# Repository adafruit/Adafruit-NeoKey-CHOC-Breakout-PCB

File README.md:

## Adafruit NeoKey CHOC Breakout PCB

<a href="http://www.adafruit.com/products/5756"><br/>
Click here to purchase one from the Adafruit shop</a>

PCB files for the Adafruit NeoKey CHOC Breakout. 

Format is EagleCAD schematic and board layout
* https://www.adafruit.com/product/5756

### Description

The only thing better than a nice mechanical key, is one that also can glow any color of the rainbow - and that's what the Adafruit NeoKey Breakout will let you do! This little 0.75" x 0.95" PCB can fit one Kailh CHOC or compatible switch and make it easy to use with a breadboard or perfboard.

The breakout has a Kailh CHOC socket, which means you can plug in any CHOC-compatible switch instead of soldering it in. You may need a little glue to keep the switch in place; hot glue or a dot of epoxy worked fine for us. We also place a 1N4148 signal diode in series with the switch, so you can create key-grid matrices without worrying about ghosted keys.

Each breakout also has a single reverse-mount NeoPixel pointing up through the spot where many switches would have an LED to shine through. The input and output of the pixel are broken out so you can 'chain' these boards together and control them as one NeoPixel strand.

There's plenty of flexibility for any kind of use; each board has the following pin out:

* VDD (+) The power pin for the NeoPixel; provide 3 to 5VDC
* GND (-) The ground power pin for the NeoPixel, connect to ground
* In (I) and Out (O) The input and output to/from the NeoPixel, for chaining
* Switch Anode (A) - The 'positive' side of the switch+diode. If you're using the switch with a pull-up resistor, connect this pin to your microcontroller. If you're using a pull-down, connect this pin to your logic level power pin.
* Switch Cathode (C) - The 'negative' side of the switch+diode. If you're using the switch with a pull-up resistor, connect this pin to ground. If you're using a pull-down, connect this pin to your microcontroller.

There're two rows of 5-pin contacts on a 0.1" grid on both sides. Solder in both sides for mechanical stability; the two sides share the same pins except for one side is NeoPixel in and the opposite side has the out pin. For side-by-side wiring, we also have the cathode pin broken out on the sides, and another set of NeoPixel In/Out pins.

Please note, each order comes with one assembled PCB and a small stick of break-off header. Soldering is required to attach the header for breadboard use. A mechanical switch and key cap are not included! Use any CHOC-compatible switch. Note that Cherry/MX switches are not at all compatible with CHOC sockets.

### License

Adafruit invests time and resources providing this open source design, please support Adafruit and open-source hardware by purchasing products from [Adafruit](https://www.adafruit.com)!

Designed by Limor Fried/Ladyada for Adafruit Industries.

Creative Commons Attribution/Share-Alike, all text above must be included in any redistribution. 
See license.txt for additional details.

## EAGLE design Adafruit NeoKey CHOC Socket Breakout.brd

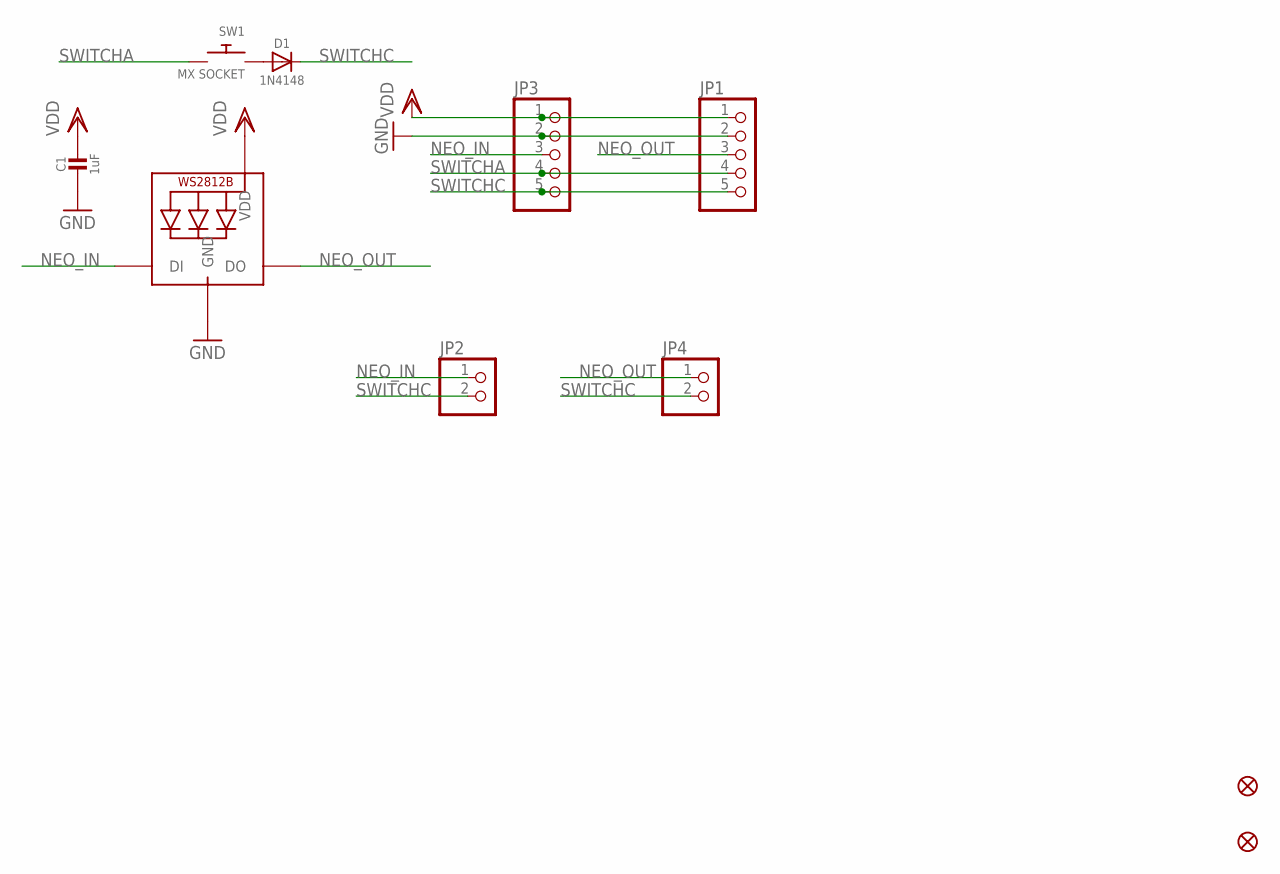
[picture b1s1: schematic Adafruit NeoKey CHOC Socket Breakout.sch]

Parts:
C1: 1uF; 0603-NO
D1: 1N4148; SOD-323
FID3, FID4: FIDUCIAL_1MM
JP1, JP3: HEADER-1X570MIL; 1X05_ROUND_70
JP2, JP4: HEADER-1X2ROUND; 1X02_ROUND
LED1: WS2812B_SK6812E; NEO3535_REVERSE
SW1: MX SOCKET; KAILH_CHOC_SOCKET

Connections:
GND: C1.2, JP1.2, JP3.2, LED1.3-GND (GND)
unnamed: D1.A, SW1.1
NEO_IN: JP2.1, JP3.3, LED1.4-DIN (DI)
NEO_OUT: JP1.3, JP4.1, LED1.2-DOUT (DO)
SWITCHA: JP1.4, JP3.4, SW1.2
SWITCHC: D1.C, JP1.5, JP2.2, JP3.5, JP4.2
VDD: C1.1, JP1.1, JP3.1, LED1.1-VDD (VDD)

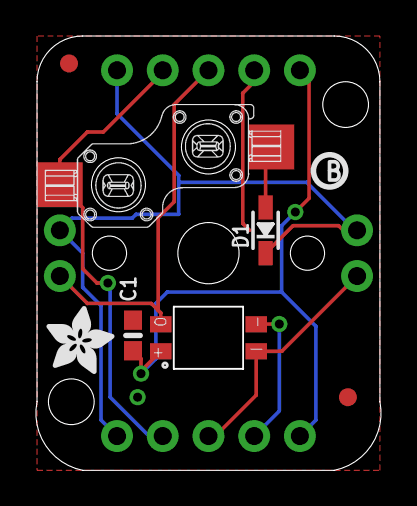
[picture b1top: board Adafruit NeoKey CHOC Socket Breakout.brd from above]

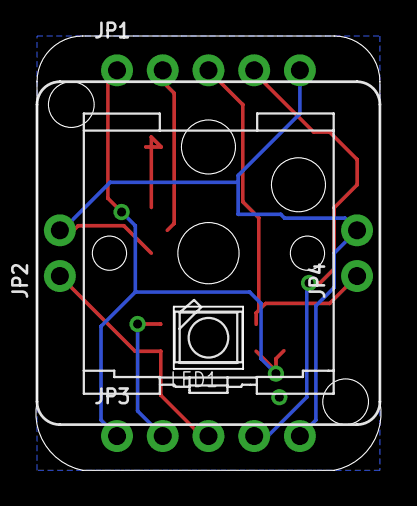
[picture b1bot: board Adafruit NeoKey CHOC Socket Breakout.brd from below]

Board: 2 copper layers, 19.1 x 24.0 mm, 37 parts (16 on the bottom side), 7 nets.

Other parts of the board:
PLABEL0, PLABEL20: PLABEL0
PLABEL1: PLABEL1
PLABEL2: PLABEL2
PLABEL3: PLABEL3
PLABEL4: PLABEL4
PLABEL5: PLABEL5
PLABEL6, PLABEL21: PLABEL6
PLABEL7: PLABEL7
PLABEL8, PLABEL22: PLABEL8
PLABEL9, PLABEL23: PLABEL9
PLABEL10: PLABEL10
PLABEL11: PLABEL11
PLABEL12: PLABEL12
PLABEL13: PLABEL13
PLABEL14: PLABEL14
PLABEL15: PLABEL15
PLABEL16: PLABEL16
PLABEL17: PLABEL17
PLABEL18: PLABEL18
PLABEL19: PLABEL19
PLABEL200: PLABEL200
U$1: PCBFEAT-REV-040
U$2: ADAFRUIT_3.5MM

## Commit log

2023-06-01 Add board files.

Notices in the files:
parts and their libraries:
microbuilder: This work is placed in the public domain, and may be freely used for commercial and non-commercial work with the following conditions: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
